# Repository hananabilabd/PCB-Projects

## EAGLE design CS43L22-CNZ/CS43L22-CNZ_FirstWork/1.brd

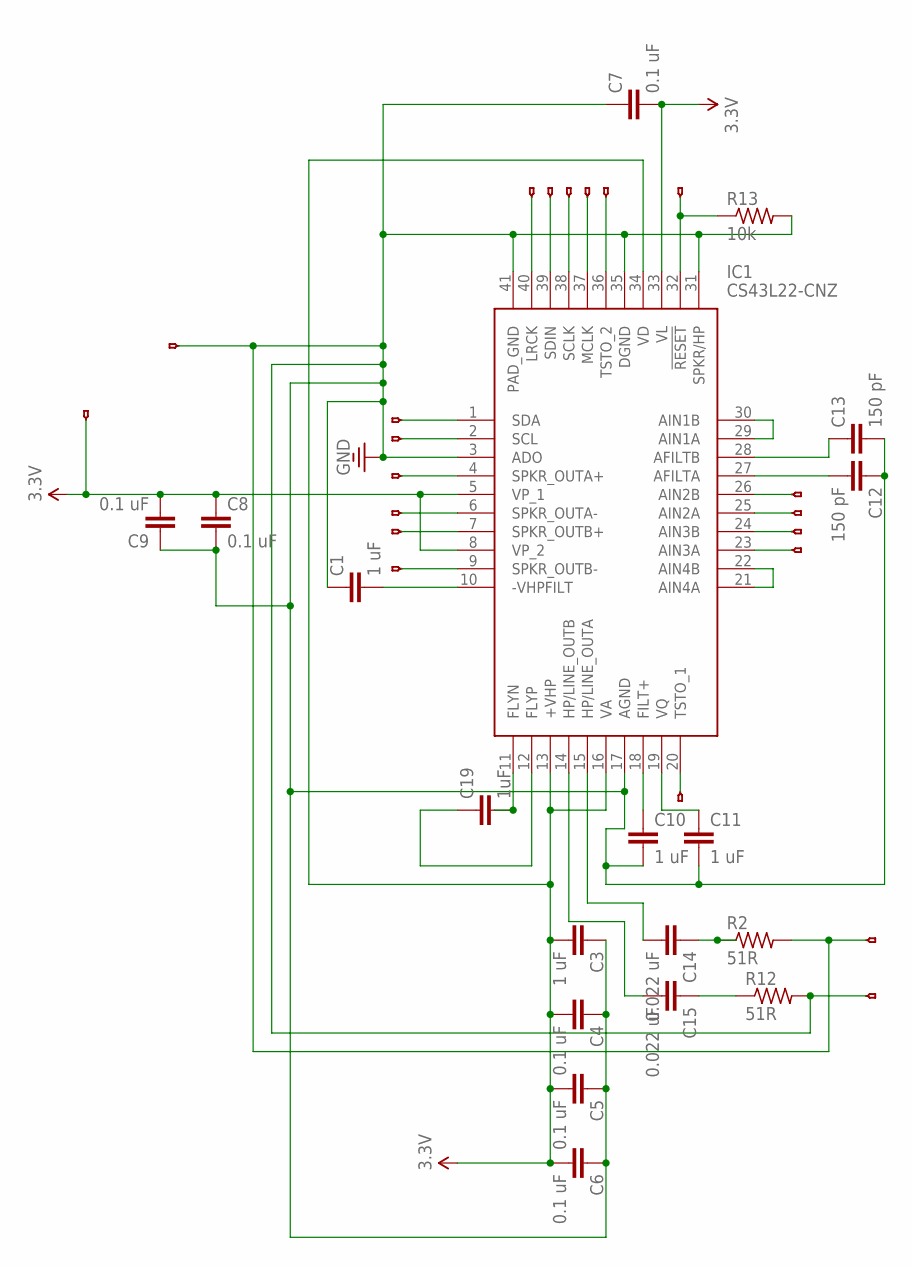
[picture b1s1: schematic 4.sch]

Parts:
C1, C3, C10, C11: 1 uF; CAP-PTH-SMALL-KIT
C4, C5, C6, C7, C8, C9: 0.1 uF; CAP-PTH-SMALL-KIT
C12, C13: 150 pF; CAP-PTH-SMALL-KIT
C14, C15: 0.022 uF; CAP-PTH-SMALL-KIT
C19: 1uF; C2.5-3
IC1: CS43L22-CNZ; QFN50P600X600X100-41N
JP1, JP2, JP3, JP4, JP5, JP6, JP7, JP8, JP9, JP10, JP11, JP12, JP13, JP14, JP15, JP16, JP17, JP18, JP19, JP23, JP24: HEADERHOLE-HEADERHOLE; 1X1-HEADER-HOLE
R2, R12: 51R; 0204V
R13: 10k; 0204V

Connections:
3.3V: C3.2, C4.2, C5.2, C6.2, C7.2, C8.1, C9.2, IC1.5 (VP_1), IC1.8 (VP_2), IC1.13 (+VHP), IC1.16 (VA), IC1.33 (VL), IC1.34 (VD), JP24.1
GND: C1.1, C3.1, C4.1, C5.1, C6.1, C7.1, C8.2, C9.1, C10.2, C11.2, C12.1, C13.2, IC1.3 (ADO), IC1.17 (AGND), IC1.31 (SPKR/HP), IC1.35 (DGND), IC1.41 (PAD_GND), JP8.1, JP9.1, JP23.1, R2.2, R12.2, R13.2; also elsewhere on the board
unnamed: C19.2, IC1.11 (FLYN)
unnamed: IC1.1 (SDA), JP1.1
unnamed: IC1.2 (SCL), JP2.1
unnamed: IC1.37 (MCLK), JP3.1
unnamed: IC1.38 (SCLK), JP4.1
unnamed: IC1.39 (SDIN), JP5.1
unnamed: IC1.40 (LRCK), JP6.1
unnamed: IC1.32 (!RESET), JP7.1, R13.1
unnamed: C1.2, IC1.10 (-VHPFILT)
unnamed: C19.1, IC1.12 (FLYP)
unnamed: C11.1, IC1.19 (VQ)
unnamed: C12.2, IC1.27 (AFILTA)
unnamed: C13.1, IC1.28 (AFILTB)
unnamed: C14.2, IC1.15 (HP/LINE_OUTA)
unnamed: C10.1, IC1.18 (FILT+)
unnamed: C15.2, IC1.14 (HP/LINE_OUTB)
unnamed: C14.1, R2.1
unnamed: C15.1, R12.1
unnamed: IC1.4 (SPKR_OUTA+), JP10.1
unnamed: IC1.6 (SPKR_OUTA-), JP11.1
unnamed: IC1.7 (SPKR_OUTB+), JP12.1
unnamed: IC1.9 (SPKR_OUTB-), JP13.1
unnamed: IC1.26 (AIN2B), JP17.1
unnamed: IC1.25 (AIN2A), JP16.1
unnamed: IC1.24 (AIN3B), JP15.1
unnamed: IC1.23 (AIN3A), JP14.1
unnamed: IC1.36 (TSTO_2), JP19.1
unnamed: IC1.20 (TSTO_1), JP18.1
unnamed 32: IC1.29 (AIN1A), IC1.30 (AIN1B); also elsewhere on the board
unnamed 33: IC1.21 (AIN4A), IC1.22 (AIN4B); also elsewhere on the board

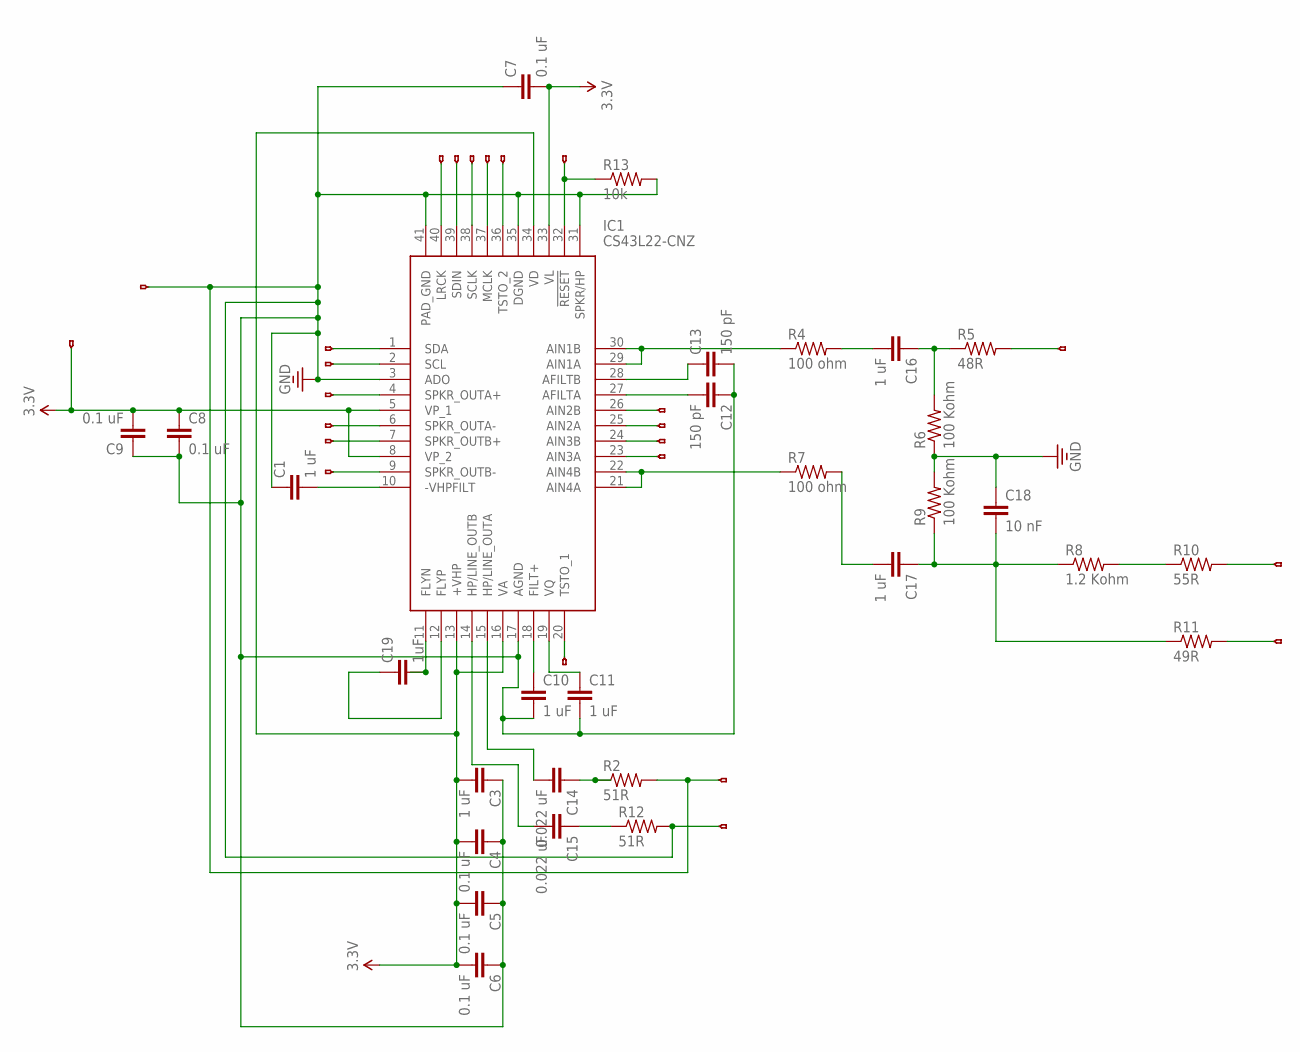
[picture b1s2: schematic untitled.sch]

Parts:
C1, C3, C10, C11, C16, C17: 1 uF; CAP-PTH-SMALL-KIT
C4, C5, C6, C7, C8, C9: 0.1 uF; CAP-PTH-SMALL-KIT
C12, C13: 150 pF; CAP-PTH-SMALL-KIT
C14, C15: 0.022 uF; CAP-PTH-SMALL-KIT
C18: 10 nF; CAP-PTH-SMALL-KIT
C19: 1uF; C2.5-3
IC1: CS43L22-CNZ; QFN50P600X600X100-41N
JP1, JP2, JP3, JP4, JP5, JP6, JP7, JP8, JP9, JP10, JP11, JP12, JP13, JP14, JP15, JP16, JP17, JP18, JP19, JP20, JP21, JP22, JP23, JP24: HEADERHOLE-HEADERHOLE; 1X1-HEADER-HOLE
R2, R12: 51R; 0204V
R4, R7: 100 ohm; 0204V
R5: 48R; 0204V
R6, R9: 100 Kohm; 0204V
R8: 1.2 Kohm; 0204V
R10: 55R; 0204V
R11: 49R; 0204V
R13: 10k; 0204V

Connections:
3.3V: C3.2, C4.2, C5.2, C6.2, C7.2, C8.1, C9.2, IC1.5 (VP_1), IC1.8 (VP_2), IC1.13 (+VHP), IC1.16 (VA), IC1.33 (VL), IC1.34 (VD), JP24.1
GND: C1.1, C3.1, C4.1, C5.1, C6.1, C7.1, C8.2, C9.1, C10.2, C11.2, C12.1, C13.2, C18.1, IC1.3 (ADO), IC1.17 (AGND), IC1.31 (SPKR/HP), IC1.35 (DGND), IC1.41 (PAD_GND), JP8.1, JP9.1, JP23.1, R2.2, R6.1, R9.2, R12.2, R13.2
unnamed: C19.2, IC1.11 (FLYN)
unnamed: IC1.1 (SDA), JP1.1
unnamed: IC1.2 (SCL), JP2.1
unnamed: IC1.37 (MCLK), JP3.1
unnamed: IC1.38 (SCLK), JP4.1
unnamed: IC1.39 (SDIN), JP5.1
unnamed: IC1.40 (LRCK), JP6.1
unnamed: IC1.32 (!RESET), JP7.1, R13.1
unnamed: C1.2, IC1.10 (-VHPFILT)
unnamed: C19.1, IC1.12 (FLYP)
unnamed: C11.1, IC1.19 (VQ)
unnamed: C16.2, R4.2
unnamed: C12.2, IC1.27 (AFILTA)
unnamed: C13.1, IC1.28 (AFILTB)
unnamed: C14.2, IC1.15 (HP/LINE_OUTA)
unnamed: C10.1, IC1.18 (FILT+)
unnamed: C15.2, IC1.14 (HP/LINE_OUTB)
unnamed: C14.1, R2.1
unnamed: C15.1, R12.1
unnamed: C16.1, R5.1, R6.2
unnamed: IC1.4 (SPKR_OUTA+), JP10.1
unnamed: IC1.6 (SPKR_OUTA-), JP11.1
unnamed: IC1.7 (SPKR_OUTB+), JP12.1
unnamed: IC1.9 (SPKR_OUTB-), JP13.1
unnamed: IC1.26 (AIN2B), JP17.1
unnamed: IC1.25 (AIN2A), JP16.1
unnamed: IC1.24 (AIN3B), JP15.1
unnamed: IC1.23 (AIN3A), JP14.1
unnamed: IC1.36 (TSTO_2), JP19.1
unnamed: IC1.20 (TSTO_1), JP18.1
unnamed: IC1.29 (AIN1A), IC1.30 (AIN1B), R4.1
unnamed: IC1.21 (AIN4A), IC1.22 (AIN4B), R7.1
unnamed: C17.2, R7.2
unnamed: JP20.1, R5.2
unnamed: C17.1, C18.2, R8.1, R9.1, R11.1
unnamed: R8.2, R10.1
unnamed: JP21.1, R10.2
unnamed: JP22.1, R11.2

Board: 2 copper layers, 54 parts (0 on the bottom side), 40 nets, no tracks yet.

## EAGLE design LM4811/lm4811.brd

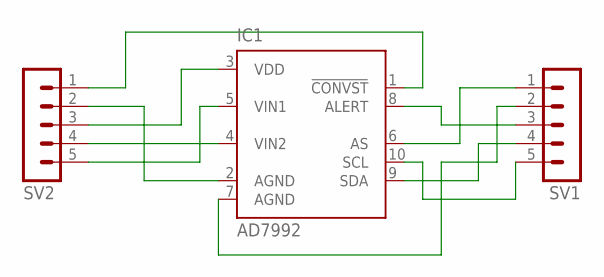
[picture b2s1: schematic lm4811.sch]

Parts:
IC1: AD7992; MSOP10
SV1, SV2: MA05-1

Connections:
unnamed: IC1.1 (!CONVST), SV2.1
unnamed: IC1.2 (AGND), SV2.2
unnamed: IC1.3 (VDD), SV2.3
unnamed: IC1.4 (VIN2), SV2.4
unnamed: IC1.5 (VIN1), SV2.5
unnamed: IC1.6 (AS), SV1.1
unnamed: IC1.7 (AGND), SV1.2
unnamed: IC1.8 (ALERT), SV1.3
unnamed: IC1.9 (SDA), SV1.4
unnamed: IC1.10 (SCL), SV1.5

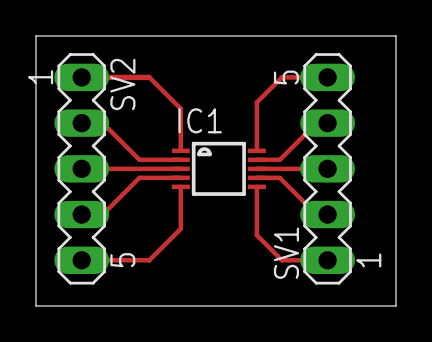
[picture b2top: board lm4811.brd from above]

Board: 2 copper layers, 20.0 x 15.0 mm, 3 parts (0 on the bottom side), 10 nets.

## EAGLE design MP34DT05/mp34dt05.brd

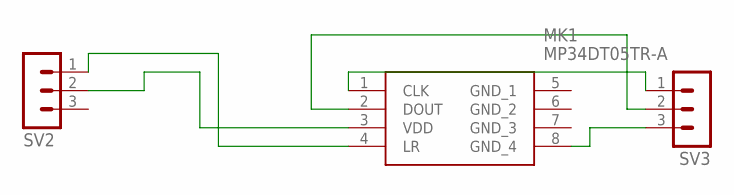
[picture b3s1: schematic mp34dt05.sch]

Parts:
MK1: MP34DT05TR-A; MP34DT05TRA
SV2, SV3: MA03-1

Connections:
unnamed: MK1.4 (LR), SV2.1
unnamed: MK1.3 (VDD), SV2.2
unnamed: MK1.1 (CLK), SV3.1
unnamed: MK1.2 (DOUT), SV3.2
unnamed: MK1.8 (GND_4), SV3.3

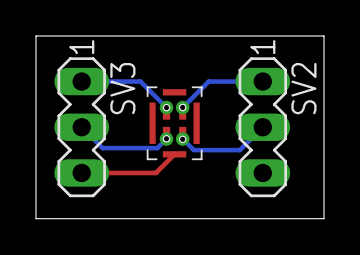
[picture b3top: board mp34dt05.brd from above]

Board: 2 copper layers, 16.0 x 10.2 mm, 3 parts (0 on the bottom side), 5 nets.
